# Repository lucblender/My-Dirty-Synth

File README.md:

# My-Dirty-Synth

Content:
 - Main Arduino code of the synth : [My-Dirty-Synth.ino](../master/My-Dirty-Synth.ino)
 - Front panel PCB in kicad 6.0 : hardware - [hardware - dirty synth folder](../master/hardware%20-%20dirty%20synth)

# Infos
This git contains all the files to realize your own "My-Dirty-Synth" made with the [Simple Synth kit](https://www.synthux.academy/simple) made by synthux academy. The synth is based on a [Daisy seed](https://www.electro-smith.com/daisy/daisy) by electro-smith and uses their Arduino library [DaisyDuino](https://github.com/electro-smith/DaisyDuino).

Each component of the synth (potentiometer, switch, jack) comes from the Simple Synth kit except what is linked to MIDI. For this, a custom PCB acting like a front panel has been made.

## Daisyduino warning

I'm using the daisysp wavefolder, it is not yet in the daisyduino library (tested the 19.04.2024 with daisyduino 1.6.3).

You need to get them in the daisysp library:
- [wavefolder.h](https://github.com/electro-smith/DaisySP/blob/master/Source/Effects/wavefolder.h)
- [wavefolder.cpp](https://github.com/electro-smith/DaisySP/blob/master/Source/Effects/wavefolder.cpp) 

You can put those two files in your daisyduino library path usually ```C:\Users\YourUserName\Documents\Arduino\libraries\DaisyDuino\src\utility\DaisySP\modules``` on Windows.

Then you'll need to do two modifications:

- on the _wavefolder.h_ file, replace line 6 ```
#include "Utility/dcblock.h"``` by ```#include "dcblock.h"```
- on the  _daisysp.h_ usually located ```C:\Users\YourUserName\Documents\Arduino\libraries\DaisyDuino\src\utility\DaisySP\daisysp.h``` you need to add ```#include "modules/wavefolder.h"``` on line 18. 

# Architecture

## Block diagram
Here is a block diagram of the synthesizer:

The design starts with an oscillator whose shape can be chosen between sinus, triangle, sawtooth, and square. In addition to the main frequency, it is possible to have the 1st and 2nd octaves mixed with the main oscillator.

The signal is then sent to the effects:
- a wavefolder 
- a decimator

Both effects have a potentiometer to drive their strength.

A 3 positions switch helps to use those two effects combined:
- position 0: wavefolder only to maximum range
- position 1: wavefolder to maximum range and decimator reduced range
- position 2: wavefolder reduced range and decimator maximum range

When passing from one mode to the other, the range of value of the effect will slowly swipe to fit the selected range. This swipe last for ~2 secs.

The next module is the filter. You can change the filter resonance, cutoff frequency, and drive. With two switch you can change from
- no filter
- high pass filter
- low pass filter
- bandpass filter.

Finally, you can find the signal can pass through a VCA or lowpass gate with attack decay and release adjustable.
You can either activate the VCA/LPG with the VCA Mode switch and then select what kind of system you want your signal to pass through:
- VCA
- LPG
- VCA+LPG

## MIDI implementation

The MIDI listens by default to **channel 1**. It reacts to changes in note On, note Off, pitch bend, and control change. 
The control change affects the filter cutoff frequency.

- Note On/Off will change the pitch. Be sure to set the oscillator's main frequency potentiometer to its minimum to avoid interference with MIDI.
- Control changes will change the cutoff frequency of the filter. Be sure to set the cutoff frequency potentiometer to its minimum to avoid interference with MIDI.

A button hooked to D13 can be used to change the MIDI channel. When pressed, the new MIDI channel will be saved according to the oscillator type and filter type switches values in binary  + 1.

For example, if you want to get MIDI channel 7, you will need to set the switch to 6 in binary 0b0110 which corresponds to Triangle oscillator and low pass filter, and then press the MIDI Channel selection button.

## Gpios
|    Bloc    |       Description       |     Components     |   Gpios   | Daisy pin | Simple Patch | Simple Pin |   Notes  |
|:----------:|:-----------------------:|:------------------:|:---------:|:---------:|:------------:|:----------:|:--------:|
| Oscillator | Main frequency          | Pot                |    A11    |     35    |       6      |     43     |          |
| Oscillator | Octave   1              | Pot                |    A10    |     32    |       8      |     40     |          |
| Oscillator | Octave   2              | Pot                |     A9    |     31    |      13      |     39     |          |
| Effects    | Wavefolder   factor     | Pot                |     A8    |     30    |      22      |     38     |          |
| Effects    | Decimator   factor      | Pot                |     A7    |     29    |      33      |     37     |          |
| Filter     | Res   frequency         | Pot                |     A6    |     28    |      42      |     36     |          |
| Filter     | Filter   drive          | Pot                |     A5    |     27    |      44      |     35     |          |
| Filter     | Filter   cutoff freq    | Pot                |     A4    |     26    |      53      |     34     |          |
| VCA/LPG    | Attack                  | Pot                |     A3    |     25    |      67      |     33     |          |
| VCA/LPG    | Release                 | Pot                |     A2    |     24    |      69      |     32     |          |
| VCA/LPG    | Decay                   | Pot                |     A1    |     23    |      73      |     31     |          |
| General    | Main   volume           | Pot                |     A0    |     22    |      71      |     30     |          |
| Oscillator | Oscillator   type       | Switch   2 pos     |     6     |     7     |       5      |      7     |          |
| Oscillator | Oscillator   type       | Switch   2 pos     |     7     |     8     |      10      |      8     |          |
| Effects    | Effect   mode selection | Switch   3 pos 1.1 |     8     |     9     |      28      |      9     |          |
| Effects    | Effect   mode selection | Switch   3 pow 1.2 |     9     |     10    |      29      |     10     |          |
| Filter     | Filter   type           | Switch   2 pos     |     10    |     11    |      50      |     11     |          |
| Filter     | Filter   type           | Switch   2 pos     |     11    |     12    |      55      |     12     |          |
| VCA/LPG    | VCA   Mode              | Switch   2 pos     |     12    |     13    |      61      |     13     |          |
| General    | Gate   out signal       | Jack               |     5     |     6     |      66      |      6     |          |
| VCA/LPG    | VCA   LPG selection     | Switch   3 pos 2.1 |     4     |     5     |      78      |      5     |          |
| VCA/LPG    | VCA   LPG selection     | Switch   3 pos 2.2 |     3     |     4     |      79      |      4     |          |
| MIDI       | MIDI Channel selection button| Button        |     13    |     14    |   (16)\*     |     14     |          |
| MIDI       | MIDI   input            | MIDI   connector   |     1     |     2     |              |            | UART     |
| Output     | AudioOut[0]             | Mono   Jack        | AudioOut1 |     18    |      76      |     18     |          |
| Output     | AudioOut[1]             | Mono   Jack        | AudioOut2 |     19    |              |            | Not used |

*The MIDI channel selection button can be put anywhere you want, accessible or not, depending on your usage. In my case, I put a discreet button on simple patch 16. I put it in this location, so it is not really visible and can be accessed through the front panel window, as shown in the following picture:

# Pictures

## Front panel design

## Wiring

# Contribution

Thanks the synthux academy community for their support and to lemkipper for contributing and putting the documentation to the test while building My-Dirty-Synth.

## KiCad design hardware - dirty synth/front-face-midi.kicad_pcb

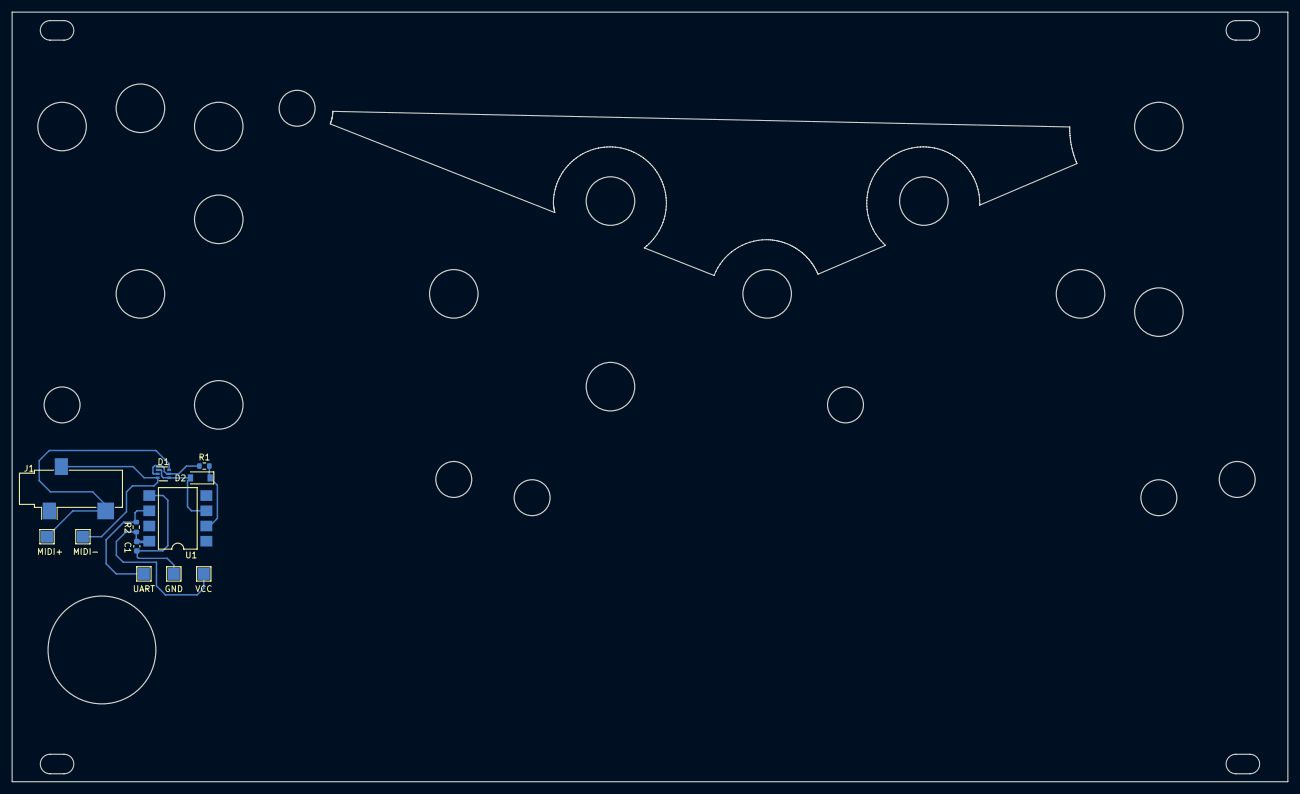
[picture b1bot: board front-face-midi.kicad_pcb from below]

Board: 2 copper layers, 213.0 x 128.5 mm, 12 parts (12 on the bottom side), 8 nets.

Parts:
C1: 100n; C_0603_1608Metric
D1: BAT54XY; SOT-363_SC-70-6
D2: 1N4148; D_SOD-123
J1: AudioJack3; Jack_3.5mm_CUI_SJ-3523-SMT_Horizontal
J2: UART; TestPoint_Pad_2.0x2.0mm
J3: GND; TestPoint_Pad_2.0x2.0mm
J4: VCC; TestPoint_Pad_2.0x2.0mm
J5: MIDI_DIN4; TestPoint_Pad_2.0x2.0mm
J6: MIDI_DIN5; TestPoint_Pad_2.0x2.0mm
R1: 220R; R_0603_1608Metric
R2: 10k; R_0603_1608Metric
U1: 6N137; SMDIP-8_W9.53mm

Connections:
+3V3: C1.1, J4.1, R2.2, U1.8 (VCC)
/uart: J2.1, R2.1, U1.6 (VO)
GND: C1.2, J3.1, U1.5 (GND)
unnamed: D1.1 (anode_1), D1.4 (anode4), D2.2 (A), U1.3 (C)
unnamed: D1.2 (cathode_2), D1.5 (cathode3), R1.2
unnamed: D1.3 (anode3/cathode4), J1.R, J5.1
unnamed: D1.6 (cathode1/anode2), J1.T, J6.1
unnamed: D2.1 (K), R1.1, U1.2 (A)

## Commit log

2022-10-25 he is da synth
2022-10-26 added midi and affinate parameters
2022-10-26 make it react to midi control change and pitch bend
2022-11-04 few minor optimisation
2022-11-20 Better wavefold and bitcrush and inverted lowpass and highpass
2022-12-11 added pcb files
2022-12-11 update links of file and folder
2022-12-11 add block diagram and gpios description
2022-12-18 Updated readme and added wiring picture
2022-12-18 fix typo in path of picture
2023-04-19 better lpg, readme with wavefolder information
    better lpg with moogladder filter by daisysp, updated readme for wavefolder integration
2023-04-19 fix broken link in readme
2023-05-06 Update README.md wiring table
2023-08-16 add default midi channel (1) and possibility to set midi channel
    Can set midi channel if you wire a button on D13. The midi channel will then be equal to the binary code + 1 of the waveform + filter switches
2023-08-16 add doc for midi channel
2023-08-16 fix doc
